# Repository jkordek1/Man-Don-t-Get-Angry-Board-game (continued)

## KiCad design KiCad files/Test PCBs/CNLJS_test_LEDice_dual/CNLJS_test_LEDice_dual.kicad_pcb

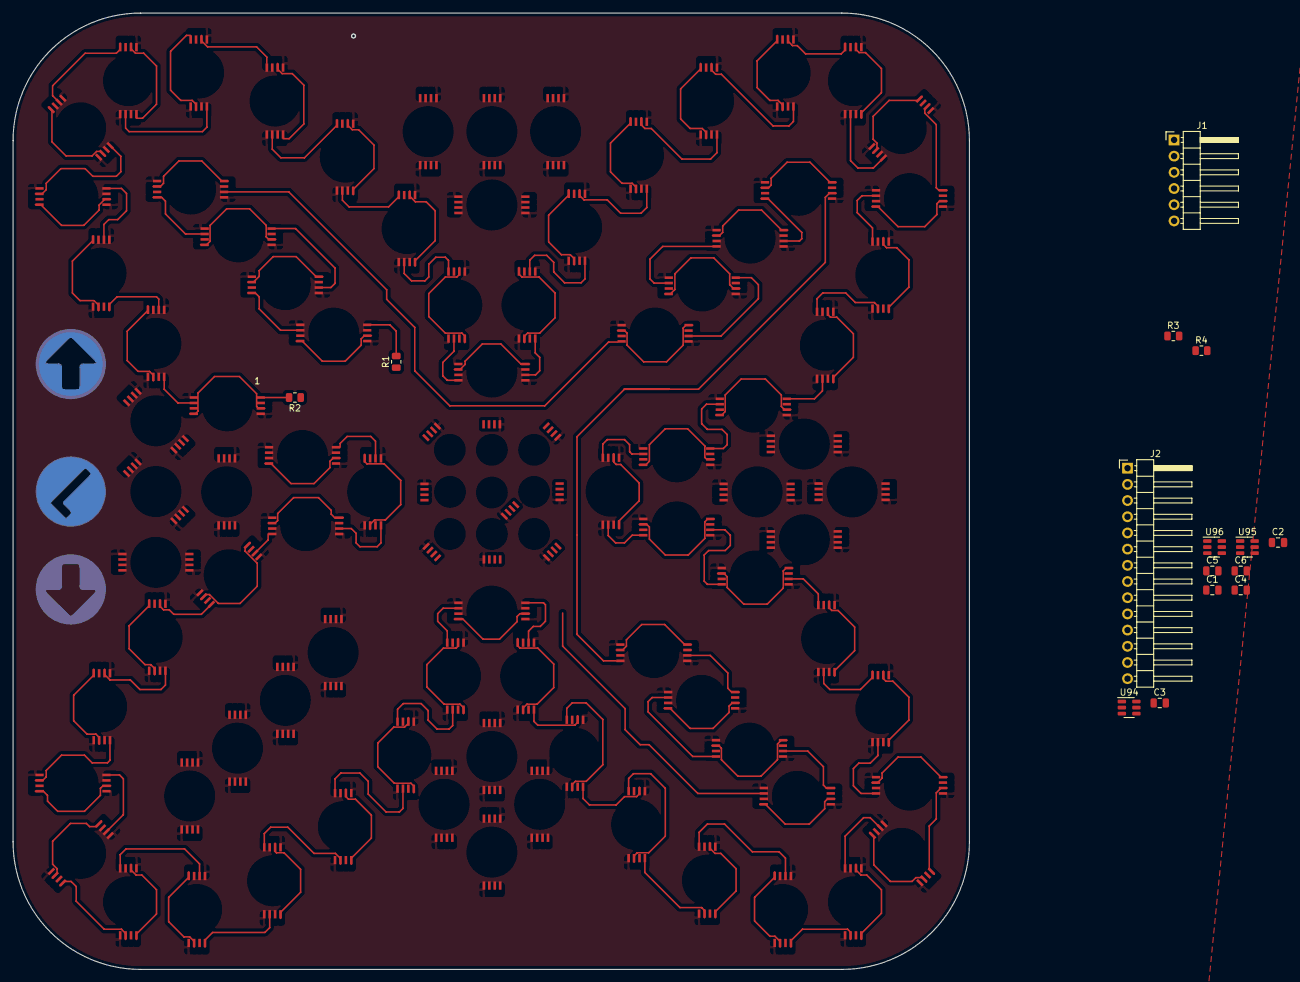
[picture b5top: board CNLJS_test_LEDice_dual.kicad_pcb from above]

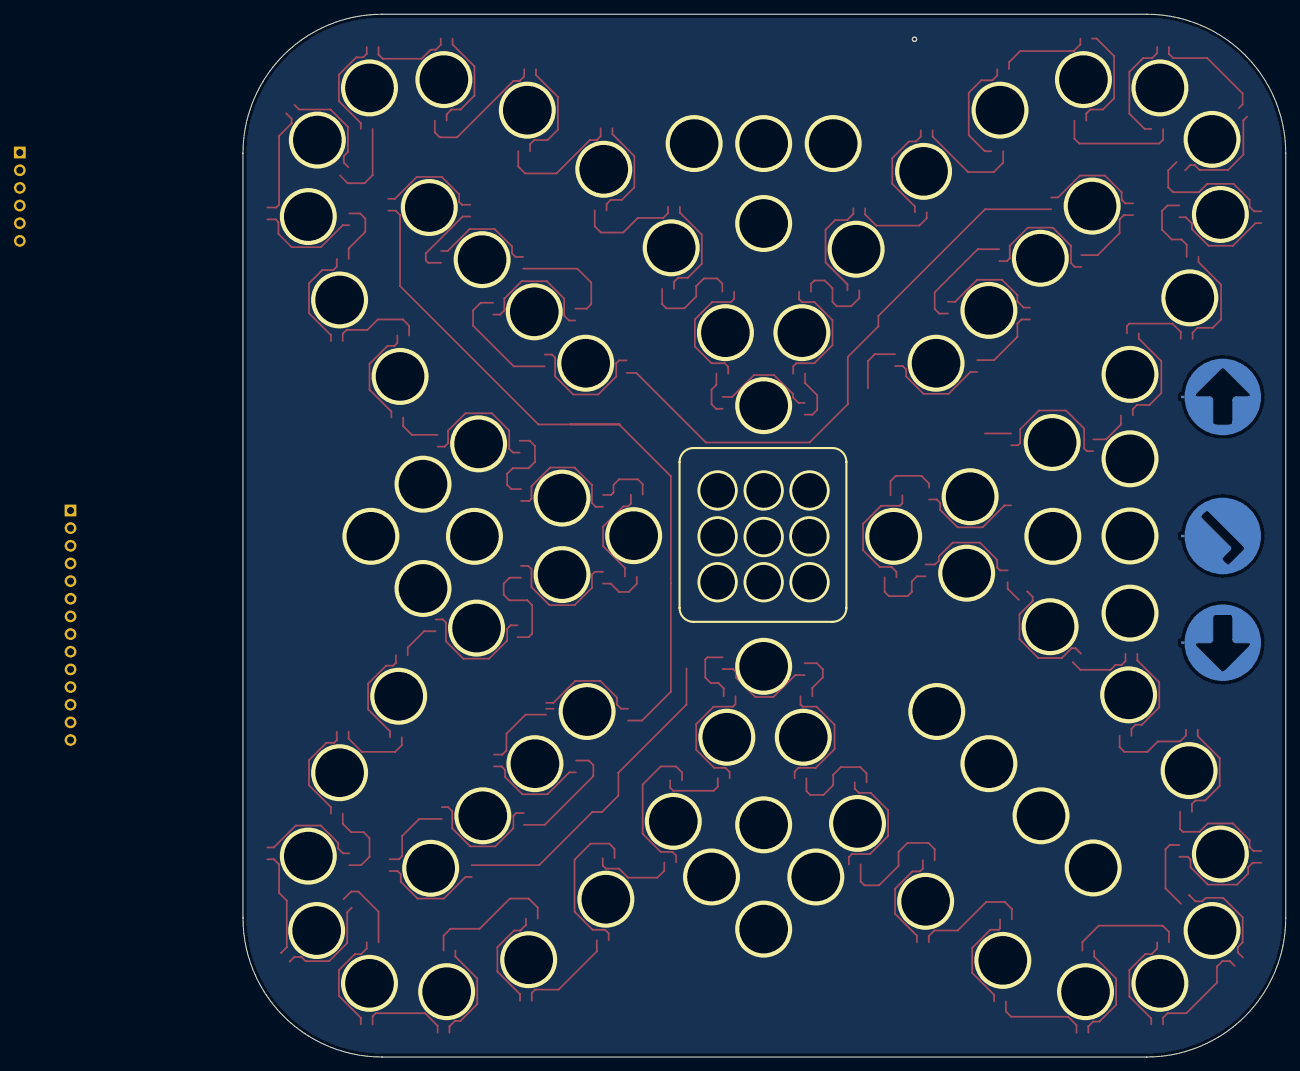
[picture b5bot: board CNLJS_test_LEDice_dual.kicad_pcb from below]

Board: 2 copper layers, 150.0 x 150.0 mm, 111 parts (3 on the bottom side), 98 nets.

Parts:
C1, C3, C5: 0-50 pF; C_0805_2012Metric
C2, C4, C6: 100n; C_0805_2012Metric
J1: Conn_01x06_Male; PinHeader_1x06_P2.54mm_Horizontal
J2: Conn_01x14_Male; PinHeader_1x14_P2.54mm_Horizontal
R1, R2, R3, R4: 470; R_0805_2012Metric
TP1: TestPoint; TP_11mm_strelicaLijevo
TP2: TestPoint; TP_11mm_kvacica
TP3: TestPoint; TP_11mm_strelicaDesno
U1, U2, U3, U4, U5, U6, U7, U8, U9, U10, U11, U12, U13, U14, U15, U16, U17, U18, U19, U20, U21, U22, U23, U24, U25, U26, U27, U28, U29, U30, U31, U32, U33, U34, U35, U36, U37, U38, U39, U40, U41, U42, U43, U44, U45, U46, U47, U48, U49, U50, U51, U52, U53, U54, U55, U56, U57, U58, U59, U60, U61, U62, U63, U64, U65, U66, U67, U68, U69, U70, U71, U72, U73, U74, U75, U76, U77, U78, U79, U80, U81, U82, U83, U84: WS2812-4020_dual; WS2812-4020-dual-7mm_bezMaske
U85, U86, U87, U88, U89, U90, U91, U92, U93: WS2812-4020_dual; WS2812-4020-single-6mm_bezMaske
U94, U95, U96: TTP223-BA6; SOT-23-6

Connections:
+5V: C2.1, C4.1, C6.1, J2.1, U94.5 (VDD), U95.5 (VDD), U96.5 (VDD)
GND: C1.2, C2.2, C3.2, C4.2, C5.2, C6.2, J1.6, J2.14, U1.4 (VSS), U2.4 (VSS), U3.4 (VSS), U4.4 (VSS), U5.4 (VSS), U6.4 (VSS), U7.4 (VSS), U8.4 (VSS), U9.4 (VSS), U10.4 (VSS), U11.4 (VSS), U12.4 (VSS), U13.4 (VSS), U14.4 (VSS), U15.4 (VSS), U16.4 (VSS), U17.4 (VSS), U18.4 (VSS), U19.4 (VSS), U20.4 (VSS), U21.4 (VSS), U22.4 (VSS), U23.4 (VSS), U24.4 (VSS), U25.4 (VSS), U26.4 (VSS), U27.4 (VSS), U28.4 (VSS), U29.4 (VSS), U30.4 (VSS), U31.4 (VSS), U32.4 (VSS), U33.4 (VSS), U34.4 (VSS), U35.4 (VSS), U36.4 (VSS), U37.4 (VSS), U38.4 (VSS), U39.4 (VSS), U40.4 (VSS), U41.4 (VSS), U42.4 (VSS), U43.4 (VSS), U44.4 (VSS), U45.4 (VSS), U46.4 (VSS), U47.4 (VSS), U48.4 (VSS), U49.4 (VSS), U50.4 (VSS), U51.4 (VSS), U52.4 (VSS), U53.4 (VSS), U54.4 (VSS), U55.4 (VSS), U56.4 (VSS), U57.4 (VSS), U58.4 (VSS), U59.4 (VSS), U60.4 (VSS), U61.4 (VSS), U62.4 (VSS), U63.4 (VSS), U64.4 (VSS), U65.4 (VSS), U66.4 (VSS), U67.4 (VSS), U68.4 (VSS), U69.4 (VSS), U70.4 (VSS), U71.4 (VSS), U72.4 (VSS), U73.4 (VSS), U74.4 (VSS), U75.4 (VSS), U76.4 (VSS), U77.4 (VSS), U78.4 (VSS), U79.4 (VSS), U80.4 (VSS), U81.4 (VSS), U82.4 (VSS), U83.4 (VSS), U84.4 (VSS), U85.4 (VSS), U86.4 (VSS), U87.4 (VSS), U88.4 (VSS), U89.4 (VSS), U90.4 (VSS), U91.4 (VSS), U92.4 (VSS), U93.4 (VSS), U94.2 (VSS), U95.2 (VSS), U96.2 (VSS)
unnamed: C1.1, TP1.1, U94.3 (I)
unnamed: C3.1, TP2.1, U95.3 (I)
unnamed: C5.1, TP3.1, U96.3 (I)
unnamed: J1.2, R1.1
unnamed: J1.3, R2.1
unnamed: J1.4, R3.1
unnamed: J1.5, R4.1
unnamed: R1.2, U1.1 (DIN)
unnamed: R2.2, U17.1 (DIN)
unnamed: R3.2, U69.1 (DIN)
unnamed: R4.2, U85.1 (DIN)
unnamed: U1.5 (DOUT), U2.1 (DIN)
unnamed: U2.5 (DOUT), U3.1 (DIN)
unnamed: U3.5 (DOUT), U4.1 (DIN)
unnamed: U4.5 (DOUT), U5.1 (DIN)
unnamed: U5.5 (DOUT), U6.1 (DIN)
unnamed: U6.5 (DOUT), U7.1 (DIN)
unnamed: U7.5 (DOUT), U8.1 (DIN)
unnamed: U8.5 (DOUT), U9.1 (DIN)
unnamed: U9.5 (DOUT), U10.1 (DIN)
unnamed: U10.5 (DOUT), U11.1 (DIN)
unnamed: U11.5 (DOUT), U12.1 (DIN)
unnamed: U12.5 (DOUT), U13.1 (DIN)
unnamed: U13.5 (DOUT), U14.1 (DIN)
unnamed: U14.5 (DOUT), U15.1 (DIN)
unnamed: U15.5 (DOUT), U16.1 (DIN)
unnamed: U17.5 (DOUT), U18.1 (DIN)
unnamed: U18.5 (DOUT), U19.1 (DIN)
unnamed: U19.5 (DOUT), U20.1 (DIN)
unnamed: U20.5 (DOUT), U21.1 (DIN)
unnamed: U21.5 (DOUT), U22.1 (DIN)
unnamed: U22.5 (DOUT), U23.1 (DIN)
unnamed: U23.5 (DOUT), U24.1 (DIN)
unnamed: U24.5 (DOUT), U25.1 (DIN)
unnamed: U25.5 (DOUT), U26.1 (DIN)
unnamed: U26.5 (DOUT), U27.1 (DIN)
unnamed: U27.5 (DOUT), U28.1 (DIN)
unnamed: U28.5 (DOUT), U29.1 (DIN)
unnamed: U29.5 (DOUT), U30.1 (DIN)
unnamed: U30.5 (DOUT), U31.1 (DIN)
unnamed: U31.5 (DOUT), U32.1 (DIN)
unnamed: U32.5 (DOUT), U33.1 (DIN)
unnamed: U33.5 (DOUT), U34.1 (DIN)
unnamed: U34.5 (DOUT), U35.1 (DIN)
unnamed: U35.5 (DOUT), U36.1 (DIN)
unnamed: U36.5 (DOUT), U37.1 (DIN)
unnamed: U37.5 (DOUT), U38.1 (DIN)
unnamed: U38.5 (DOUT), U39.1 (DIN)
unnamed: U39.5 (DOUT), U40.1 (DIN)
unnamed: U40.5 (DOUT), U41.1 (DIN)
unnamed: U41.5 (DOUT), U42.1 (DIN)
unnamed: U42.5 (DOUT), U43.1 (DIN)
unnamed: U43.5 (DOUT), U44.1 (DIN)
unnamed: U44.5 (DOUT), U45.1 (DIN)
unnamed: U45.5 (DOUT), U46.1 (DIN)
unnamed: U46.5 (DOUT), U47.1 (DIN)
unnamed: U47.5 (DOUT), U48.1 (DIN)
unnamed: U48.5 (DOUT), U49.1 (DIN)
unnamed: U49.5 (DOUT), U50.1 (DIN)
unnamed: U50.5 (DOUT), U51.1 (DIN)
unnamed: U51.5 (DOUT), U52.1 (DIN)
unnamed: U52.5 (DOUT), U53.1 (DIN)
unnamed: U53.5 (DOUT), U54.1 (DIN)
unnamed: U54.5 (DOUT), U55.1 (DIN)
unnamed: U55.5 (DOUT), U56.1 (DIN)
unnamed: U56.5 (DOUT), U57.1 (DIN)
unnamed: U57.5 (DOUT), U58.1 (DIN)
unnamed: U58.5 (DOUT), U59.1 (DIN)
unnamed: U59.5 (DOUT), U60.1 (DIN)
unnamed: U60.5 (DOUT), U61.1 (DIN)
unnamed: U61.5 (DOUT), U62.1 (DIN)
unnamed: U62.5 (DOUT), U63.1 (DIN)
unnamed: U63.5 (DOUT), U64.1 (DIN)
unnamed: U64.5 (DOUT), U65.1 (DIN)
unnamed: U65.5 (DOUT), U66.1 (DIN)
unnamed: U66.5 (DOUT), U67.1 (DIN)
unnamed: U67.5 (DOUT), U68.1 (DIN)
unnamed: U69.5 (DOUT), U70.1 (DIN)
unnamed: U70.5 (DOUT), U71.1 (DIN)
unnamed: U71.5 (DOUT), U72.1 (DIN)
unnamed: U72.5 (DOUT), U73.1 (DIN)
unnamed: U73.5 (DOUT), U74.1 (DIN)
unnamed: U74.5 (DOUT), U75.1 (DIN)
unnamed: U75.5 (DOUT), U76.1 (DIN)
unnamed: U76.5 (DOUT), U77.1 (DIN)
unnamed: U77.5 (DOUT), U78.1 (DIN)
unnamed: U78.5 (DOUT), U79.1 (DIN)
unnamed: U79.5 (DOUT), U80.1 (DIN)
unnamed: U80.5 (DOUT), U81.1 (DIN)
unnamed: U81.5 (DOUT), U82.1 (DIN)
unnamed: U82.5 (DOUT), U83.1 (DIN)
unnamed: U83.5 (DOUT), U84.1 (DIN)
TP1: J2.2, U94.1 (Q)
TP2: J2.3, U95.1 (Q)
TP3: J2.4, U96.1 (Q)
VDD: J1.1, U1.2 (VDD), U2.2 (VDD), U3.2 (VDD), U4.2 (VDD), U5.2 (VDD), U6.2 (VDD), U7.2 (VDD), U8.2 (VDD), U9.2 (VDD), U10.2 (VDD), U11.2 (VDD), U12.2 (VDD), U13.2 (VDD), U14.2 (VDD), U15.2 (VDD), U16.2 (VDD), U17.2 (VDD), U18.2 (VDD), U19.2 (VDD), U20.2 (VDD), U21.2 (VDD), U22.2 (VDD), U23.2 (VDD), U24.2 (VDD), U25.2 (VDD), U26.2 (VDD), U27.2 (VDD), U28.2 (VDD), U29.2 (VDD), U30.2 (VDD), U31.2 (VDD), U32.2 (VDD), U33.2 (VDD), U34.2 (VDD), U35.2 (VDD), U36.2 (VDD), U37.2 (VDD), U38.2 (VDD), U39.2 (VDD), U40.2 (VDD), U41.2 (VDD), U42.2 (VDD), U43.2 (VDD), U44.2 (VDD), U45.2 (VDD), U46.2 (VDD), U47.2 (VDD), U48.2 (VDD), U49.2 (VDD), U50.2 (VDD), U51.2 (VDD), U52.2 (VDD), U53.2 (VDD), U54.2 (VDD), U55.2 (VDD), U56.2 (VDD), U57.2 (VDD), U58.2 (VDD), U59.2 (VDD), U60.2 (VDD), U61.2 (VDD), U62.2 (VDD), U63.2 (VDD), U64.2 (VDD), U65.2 (VDD), U66.2 (VDD), U67.2 (VDD), U68.2 (VDD), U69.2 (VDD), U70.2 (VDD), U71.2 (VDD), U72.2 (VDD), U73.2 (VDD), U74.2 (VDD), U75.2 (VDD), U76.2 (VDD), U77.2 (VDD), U78.2 (VDD), U79.2 (VDD), U80.2 (VDD), U81.2 (VDD), U82.2 (VDD), U83.2 (VDD), U84.2 (VDD), U85.2 (VDD), U86.2 (VDD), U87.2 (VDD), U88.2 (VDD), U89.2 (VDD), U90.2 (VDD), U91.2 (VDD), U92.2 (VDD), U93.2 (VDD)

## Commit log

2022-02-09 Initial
2022-02-09 Schematic
2022-02-09 More PCBS
2022-02-09 New images
2022-02-12 test_1
2022-03-18 test
2022-03-21 cnljs
2022-04-15 backup
2022-04-15 layout
2022-04-19 route
2022-04-19 FieldBoard created
2022-04-19 delete
2022-04-19 FieldBoard
2022-04-26 layout v1
2022-06-20 touchpad_v2
2022-06-29 update v2
2022-07-03 buzzer footprint
2022-07-03 shematic update
2022-07-06 buzzer
2022-09-23 Update fp-info-cache
2022-10-18 Script
2022-10-26 layout_v2
2022-11-04 Kockica
2022-11-08 to-do added
2022-11-14 Remove old files
2022-11-15 Documentation
2022-11-23 Schematic update
2023-04-18 Images Initial release
2024-02-29 kicad8
2026-01-29 Images
